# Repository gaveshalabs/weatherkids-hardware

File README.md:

# WeatherKids Weather Computer

WeatherKids is an engaging climate education program where children learn about climate change hands-on using a small, open-source weather station called the **Weather Computer**. This repository contains source code for both versions, **v1.0** and **v2.0**, of the Weather Computer. It is licensed under the **CERN Open Hardware License - W**, making it free to use, modify, and share in compliance with the license terms.

## Overview

The WeatherKids Weather Computer is designed to help young learners understand key aspects of weather and climate. Through real-time data collection and analysis, children learn about:

- Temperature
- Humidity
- Atmospheric Pressure
- And optional TVOC sensor

These metrics contribute to building awareness around climate science and inspire further exploration in STEM.

## Versions

### Version 1.0
- **Released**: 2022 December
- **Features**: 
    - Basic weather measurements (temperature, humidity,  pressure and optional TVOC sensor)
 
KNOWN issues - Charging mechanism doesn't work properly in fog conditions

### Version 2.0
- **Released**: 2023 December
- **Features**: 
    - Compact design with Li-Polimer battery
    - Sperate Action card to mearsure solar power and provide power to main board.

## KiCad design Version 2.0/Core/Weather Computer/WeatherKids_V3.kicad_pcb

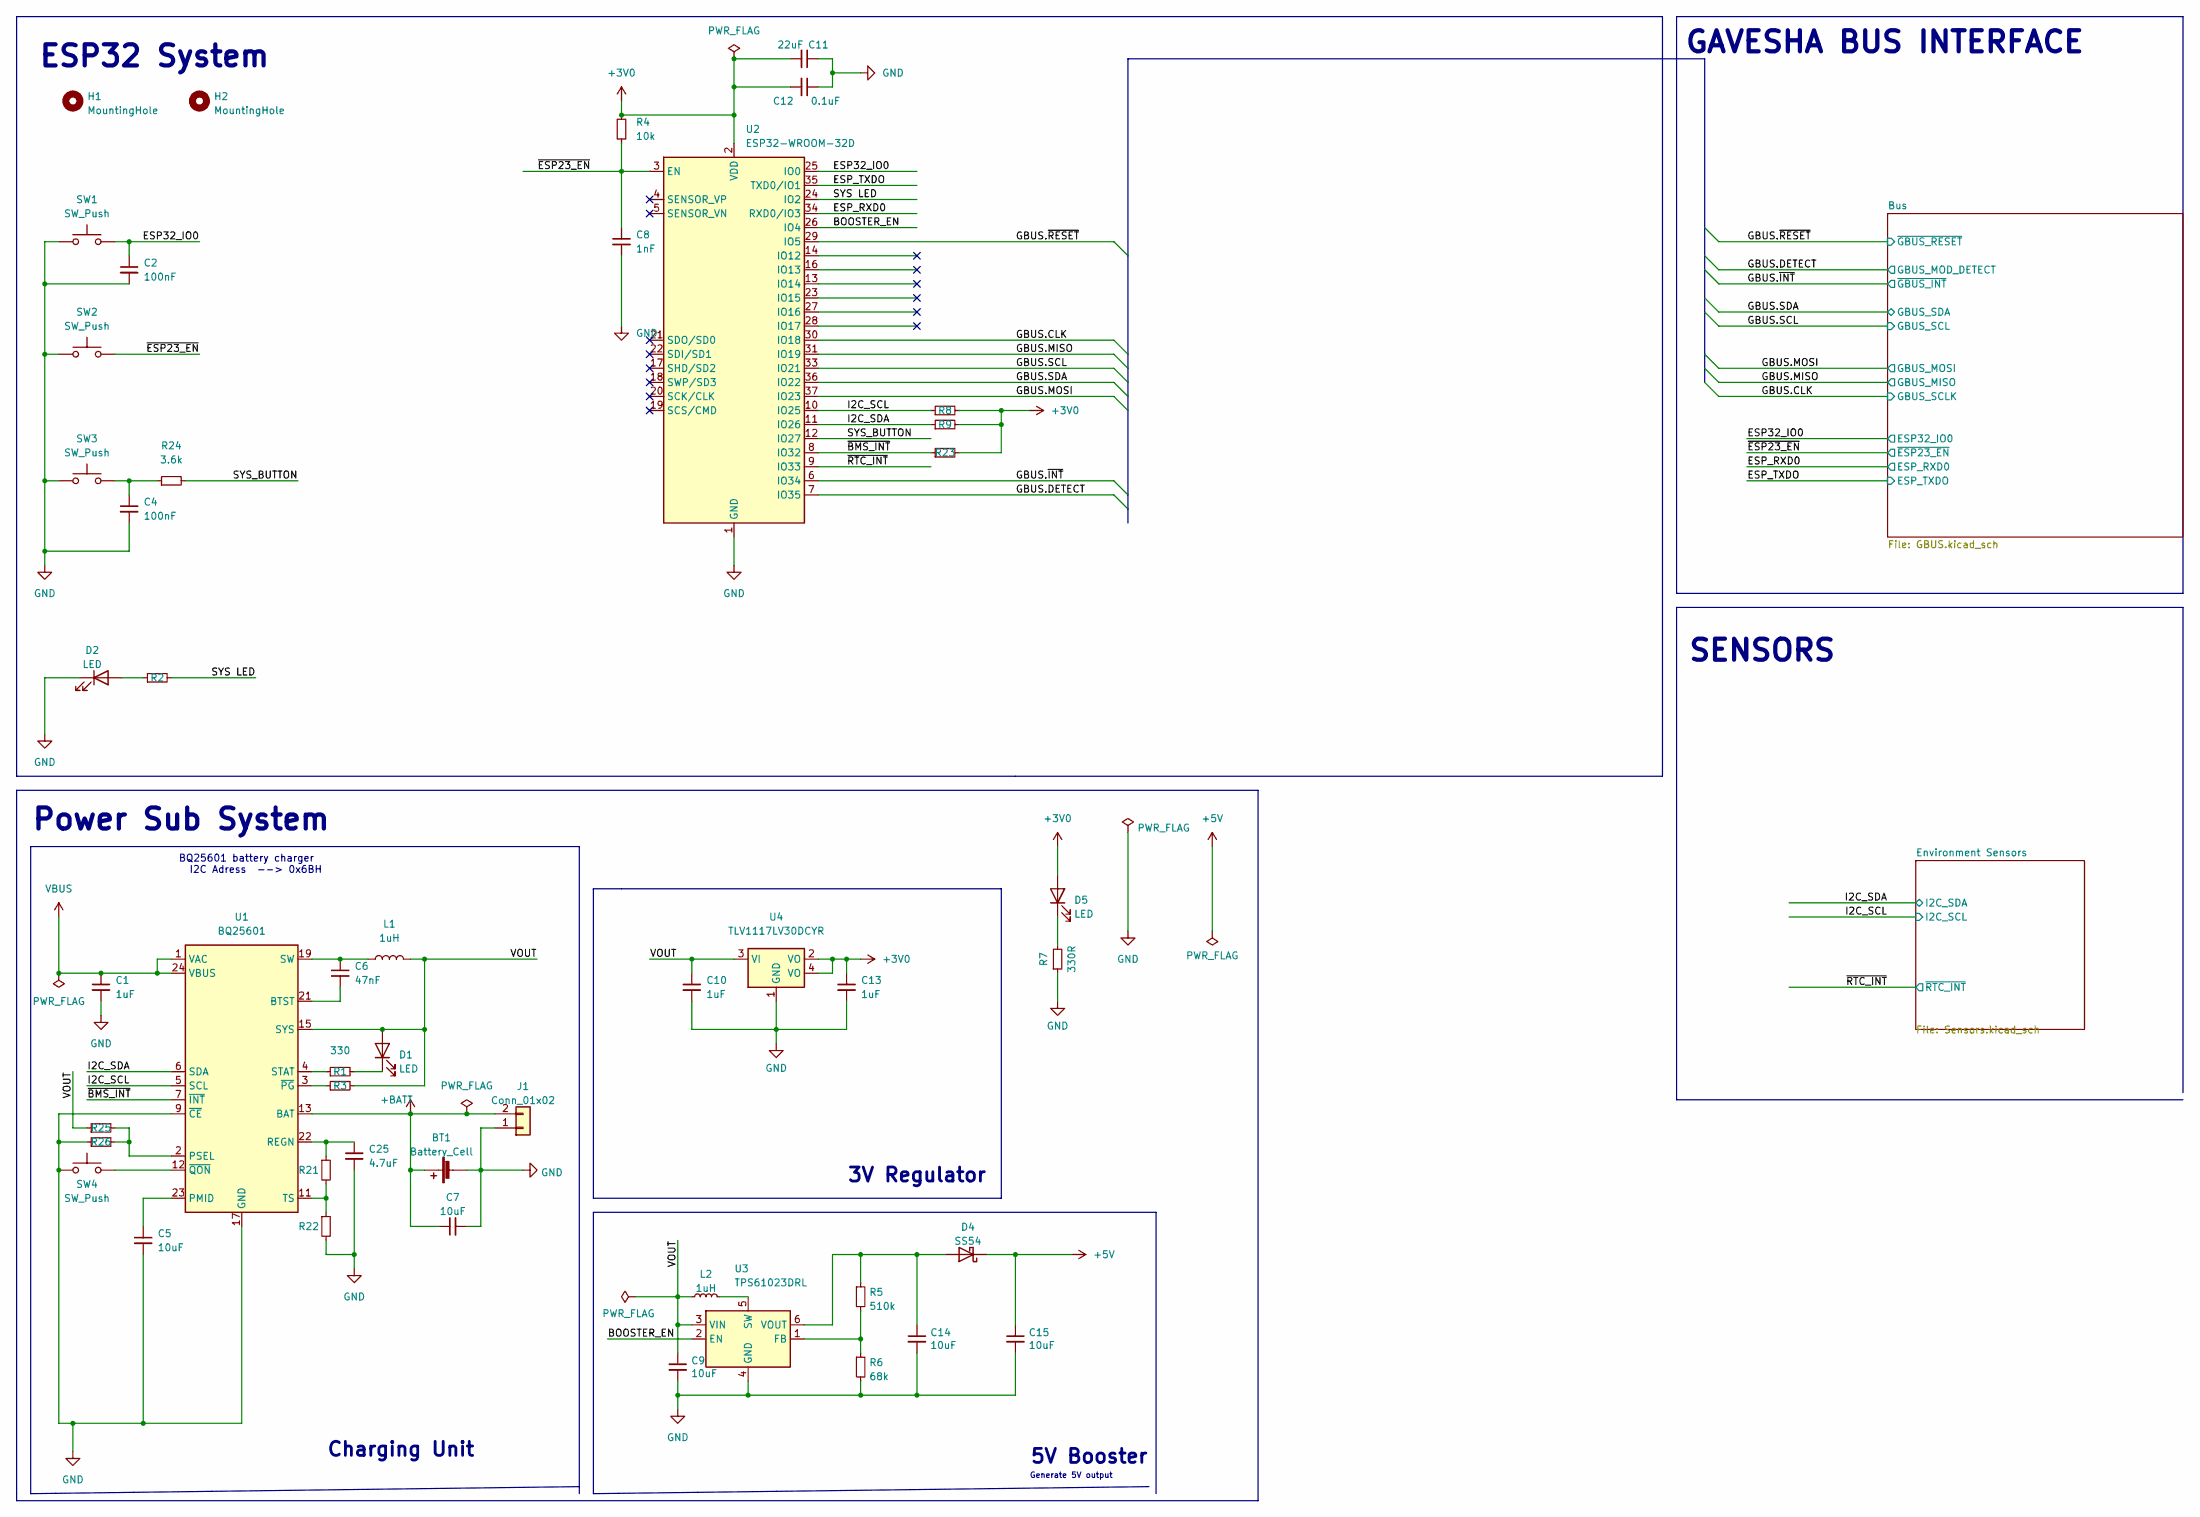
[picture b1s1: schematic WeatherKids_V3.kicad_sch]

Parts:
BT1: Battery_Cell; BatteryHolder_Keystone_1042_1x18650
C1, C10, C13: 1uF; C_0402_1005Metric
C2, C4: 100nF; C_0402_1005Metric
C5: 10uF; C_0402_1005Metric
C6: 47nF; C_0603_1608Metric
C7, C9, C14, C15: 10uF; C_0805_2012Metric
C8: 1nF; C_0402_1005Metric
C11: 22uF; C_0603_1608Metric
C12: 0.1uF; C_0402_1005Metric
C25: 4.7uF; C_0402_1005Metric
D1, D2, D5: LED; LED_0805_2012Metric
D4: SS54; D_SMA
H1, H2: MountingHole; MountingHole_2.2mm_M2
J1: Conn_01x02; JST_PH_S2B-PH-SM4-TB_1x02-1MP_P2.00mm_Horizontal
L1, L2: 1uH; WPN252010U
R1: 330; R_0402_1005Metric
R2, R7: 330R; R_0402_1005Metric
R3, R4, R8, R9, R21, R22, R23, R25, R26: 10k; R_0402_1005Metric
R5: 510k; R_0402_1005Metric
R6: 68k; R_0402_1005Metric
R24: 3.6k; R_0402_1005Metric
SW1, SW2, SW3, SW4: SW_Push; SKRTLB
U1: BQ25601; Texas_S-PWQFN-N24_EP2.7x2.7mm_ThermalVias
U2: ESP32-WROOM-32D; ESP32-WROOM-32
U3: TPS61023DRL; DRL0006A
U4: TLV1117LV30DCYR; SOT-223

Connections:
+3V0: C11.2, C12.2, C13.1, D5.2 (A), R4.1, R8.2, R9.2, R23.2, U2.2 (VDD), U4.2 (VO), U4.4 (VO); also elsewhere on the board
+5V: C15.1, D4.1 (K); also elsewhere on the board
+BATT: BT1.1 (+), C7.1, J1.2, U1.13 (BAT), U1.14 (BAT); also elsewhere on the board
/BOOSTER_EN: U2.26 (IO4), U3.2 (EN)
/ESP32_IO0: C2.1, SW1.2, U2.25 (IO0); also elsewhere on the board
/ESP_RXD0: U2.34 (RXD0/IO3); also elsewhere on the board
/ESP_TXDO: U2.35 (TXD0/IO1); also elsewhere on the board
/GBUS.CLK: U2.30 (IO18); also elsewhere on the board
/GBUS.DETECT: U2.7 (IO35); also elsewhere on the board
/GBUS.MISO: U2.31 (IO19); also elsewhere on the board
/GBUS.MOSI: U2.37 (IO23); also elsewhere on the board
/GBUS.SCL: U2.33 (IO21); also elsewhere on the board
/GBUS.SDA: U2.36 (IO22); also elsewhere on the board
/GBUS.~INT: U2.6 (IO34); also elsewhere on the board
/GBUS.~RESET: U2.29 (IO5); also elsewhere on the board
/I2C_SCL: R8.1, U1.5 (SCL), U2.10 (IO25); also elsewhere on the board
/I2C_SDA: R9.1, U1.6 (SDA), U2.11 (IO26); also elsewhere on the board
/SYS LED: R2.2, U2.24 (IO2)
/SYS_BUTTON: R24.2, U2.12 (IO27)
/VOUT: C9.1, C10.1, D1.2 (A), L1.2, L2.1, R3.2, R25.1, U1.15 (SYS), U1.16 (SYS), U3.3 (VIN), U4.3 (VI)
/~BMS_INT: R23.1, U1.7 (~INT), U2.8 (IO32)
/~ESP23_EN: C8.1, R4.2, SW2.2, U2.3 (EN); also elsewhere on the board
/~RTC_INT: U2.9 (IO33); also elsewhere on the board
GND: BT1.2 (-), C1.2, C2.2, C4.2, C5.2, C7.2, C8.2, C9.2, C10.2, C11.1, C12.1, C13.2, C14.2, C15.2, C25.2, D2.1 (K), J1.1, R6.2, R7.1, R22.2, R26.1, SW1.1, SW2.1, SW3.1, SW4.1, U1.9 (~CE), U1.17 (GND), U1.18 (GND), U1.25 (GND), U2.1 (GND), U2.15 (GND), U2.38 (GND), U2.39 (GND), U3.4 (GND), U4.1 (GND); also elsewhere on the board
unnamed: C4.1, R24.1, SW3.2
unnamed: C5.1, U1.23 (PMID)
unnamed: C6.1, L1.1, U1.19 (SW), U1.20 (SW)
unnamed: C6.2, U1.21 (BTST)
unnamed: C14.1, D4.2 (A), R5.1, U3.6 (VOUT)
unnamed: C25.1, R21.1, U1.22 (REGN)
unnamed: D1.1 (K), R1.2
unnamed: D2.2 (A), R2.1
unnamed: D5.1 (K), R7.2
unnamed: L2.2, U3.5 (SW)
unnamed: R1.1, U1.4 (STAT)
unnamed: R3.1, U1.3 (~PG)
unnamed: R5.2, R6.1, U3.1 (FB)
unnamed: R21.2, R22.1, U1.11 (TS)
unnamed: R25.2, R26.2, U1.2 (PSEL)
unnamed: SW4.2, U1.12 (~QON)
VBUS: C1.1, U1.1 (VAC), U1.24 (VBUS); also elsewhere on the board

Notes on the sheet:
5V Booster
SENSORS
Power Sub System
ESP32 System
3V Regulator
BQ25601 battery charger I2C Adress --> 0x6BH
Charging Unit
Generate 5V output
GAVESHA BUS INTERFACE

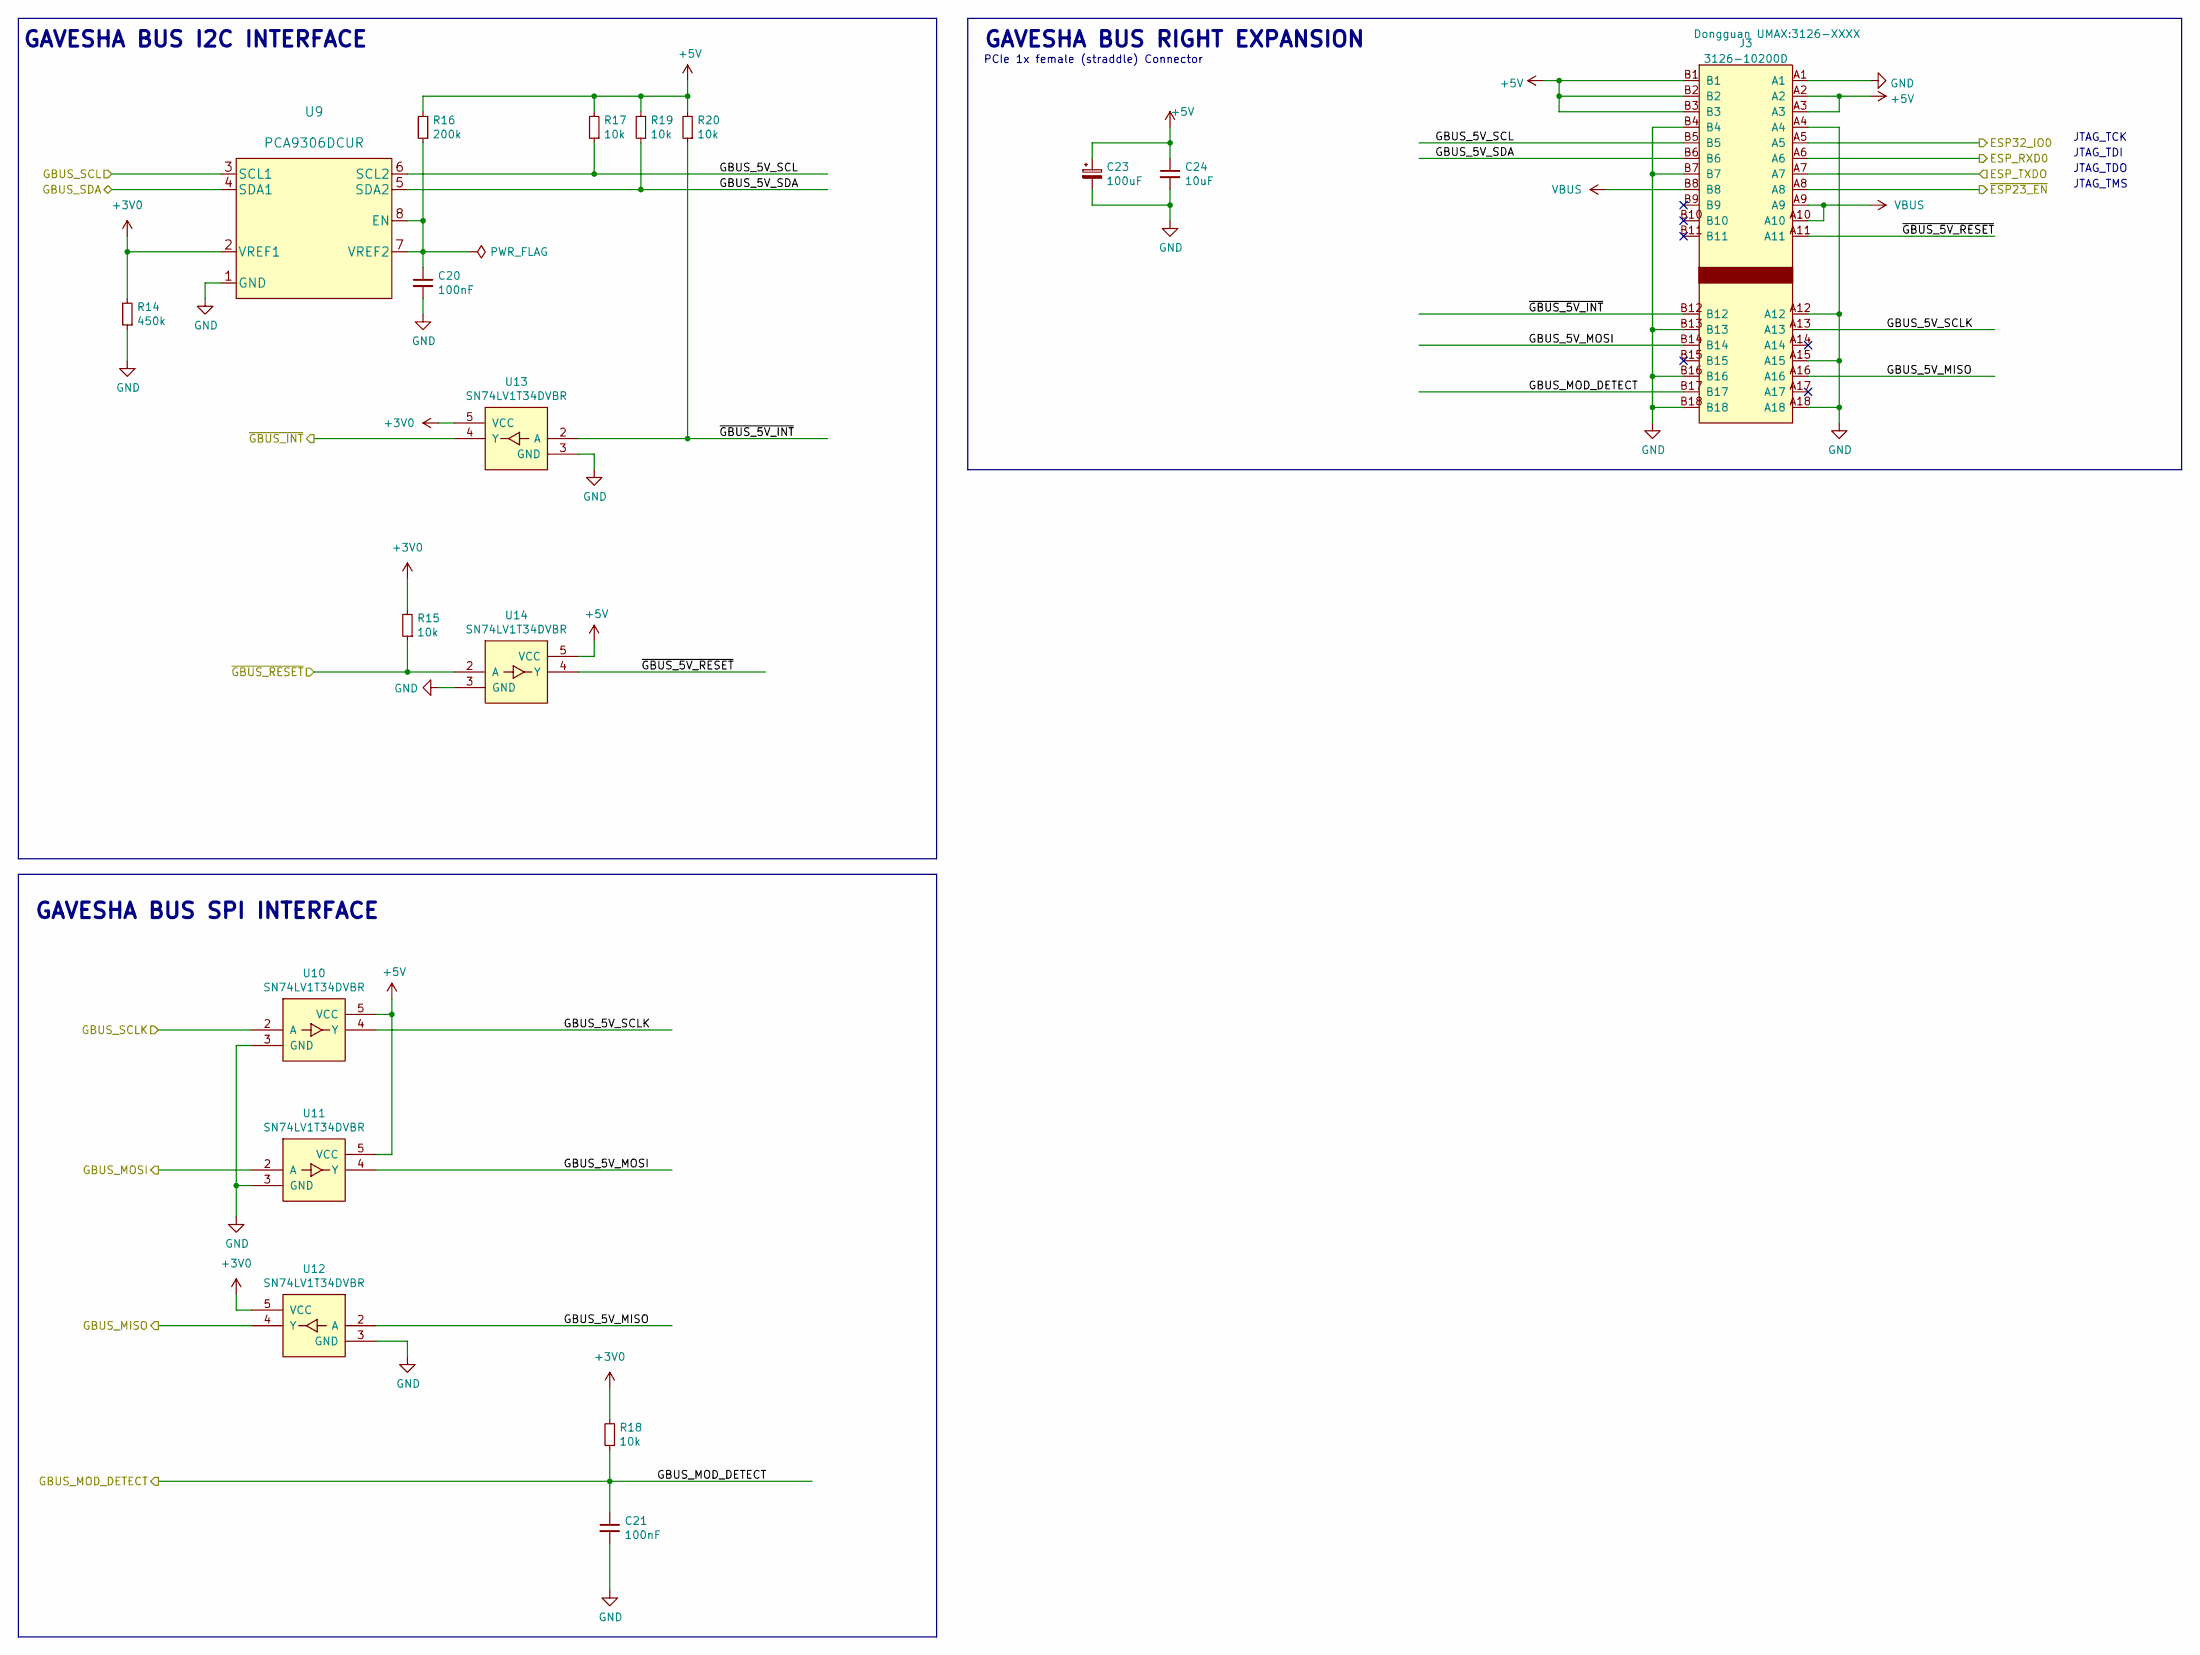
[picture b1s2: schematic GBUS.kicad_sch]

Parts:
C20, C21: 100nF; C_0402_1005Metric
C23: 100uF; CP_EIA-3528-12_Kemet-T
C24: 10uF; C_0805_2012Metric
J3: 3126-10200D; 3126-XXXX
R14: 450k; R_0402_1005Metric
R15, R17, R18, R19, R20: 10k; R_0402_1005Metric
R16: 200k; R_0402_1005Metric
U9: PCA9306DCUR
U10, U11, U12, U13, U14: SN74LV1T34DVBR; SOT-23-5

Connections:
+3V0: R14.2, R15.2, R18.2, U9.2 (VREF1), U12.5 (VCC), U13.5 (VCC); also elsewhere on the board
+5V: C23.1, C24.1, J3.A2, J3.A3, J3.B1, J3.B2, J3.B3, R16.2, R17.2, R19.2, R20.2, U10.5 (VCC), U11.5 (VCC), U14.5 (VCC); also elsewhere on the board
/Bus/GBUS_5V_MISO: J3.A16, U12.2 (A)
/Bus/GBUS_5V_MOSI: J3.B14, U11.4 (Y)
/Bus/GBUS_5V_SCL: J3.B5, R17.1, U9.6 (SCL2)
/Bus/GBUS_5V_SCLK: J3.A13, U10.4 (Y)
/Bus/GBUS_5V_SDA: J3.B6, R19.1, U9.5 (SDA2)
/Bus/~GBUS_5V_INT: J3.B12, R20.1, U13.2 (A)
/Bus/~GBUS_5V_RESET: J3.A11, U14.4 (Y)
/ESP32_IO0: J3.A5; also elsewhere on the board
/ESP_RXD0: J3.A6; also elsewhere on the board
/ESP_TXDO: J3.A7; also elsewhere on the board
/GBUS.CLK: U10.2 (A); also elsewhere on the board
/GBUS.DETECT: C21.1, J3.B17, R18.1; also elsewhere on the board
/GBUS.MISO: U12.4 (Y); also elsewhere on the board
/GBUS.MOSI: U11.2 (A); also elsewhere on the board
/GBUS.SCL: U9.3 (SCL1); also elsewhere on the board
/GBUS.SDA: U9.4 (SDA1); also elsewhere on the board
/GBUS.~INT: U13.4 (Y); also elsewhere on the board
/GBUS.~RESET: R15.1, U14.2 (A); also elsewhere on the board
/~ESP23_EN: J3.A8; also elsewhere on the board
GND: C20.2, C21.2, C23.2, C24.2, J3.A1, J3.A4, J3.A12, J3.A15, J3.A18, J3.B4, J3.B7, J3.B13, J3.B16, J3.B18, R14.1, U9.1 (GND), U10.3 (GND), U11.3 (GND), U12.3 (GND), U13.3 (GND), U14.3 (GND); also elsewhere on the board
unnamed: C20.1, R16.1, U9.7 (VREF2), U9.8 (EN)
VBUS: J3.A9, J3.A10, J3.B8; also elsewhere on the board

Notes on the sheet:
GAVESHA BUS I2C INTERFACE
JTAG_TDO
GAVESHA BUS SPI INTERFACE
JTAG_TDI
JTAG_TCK
PCIe 1x female (straddle) Connector
GAVESHA BUS RIGHT EXPANSION
JTAG_TMS

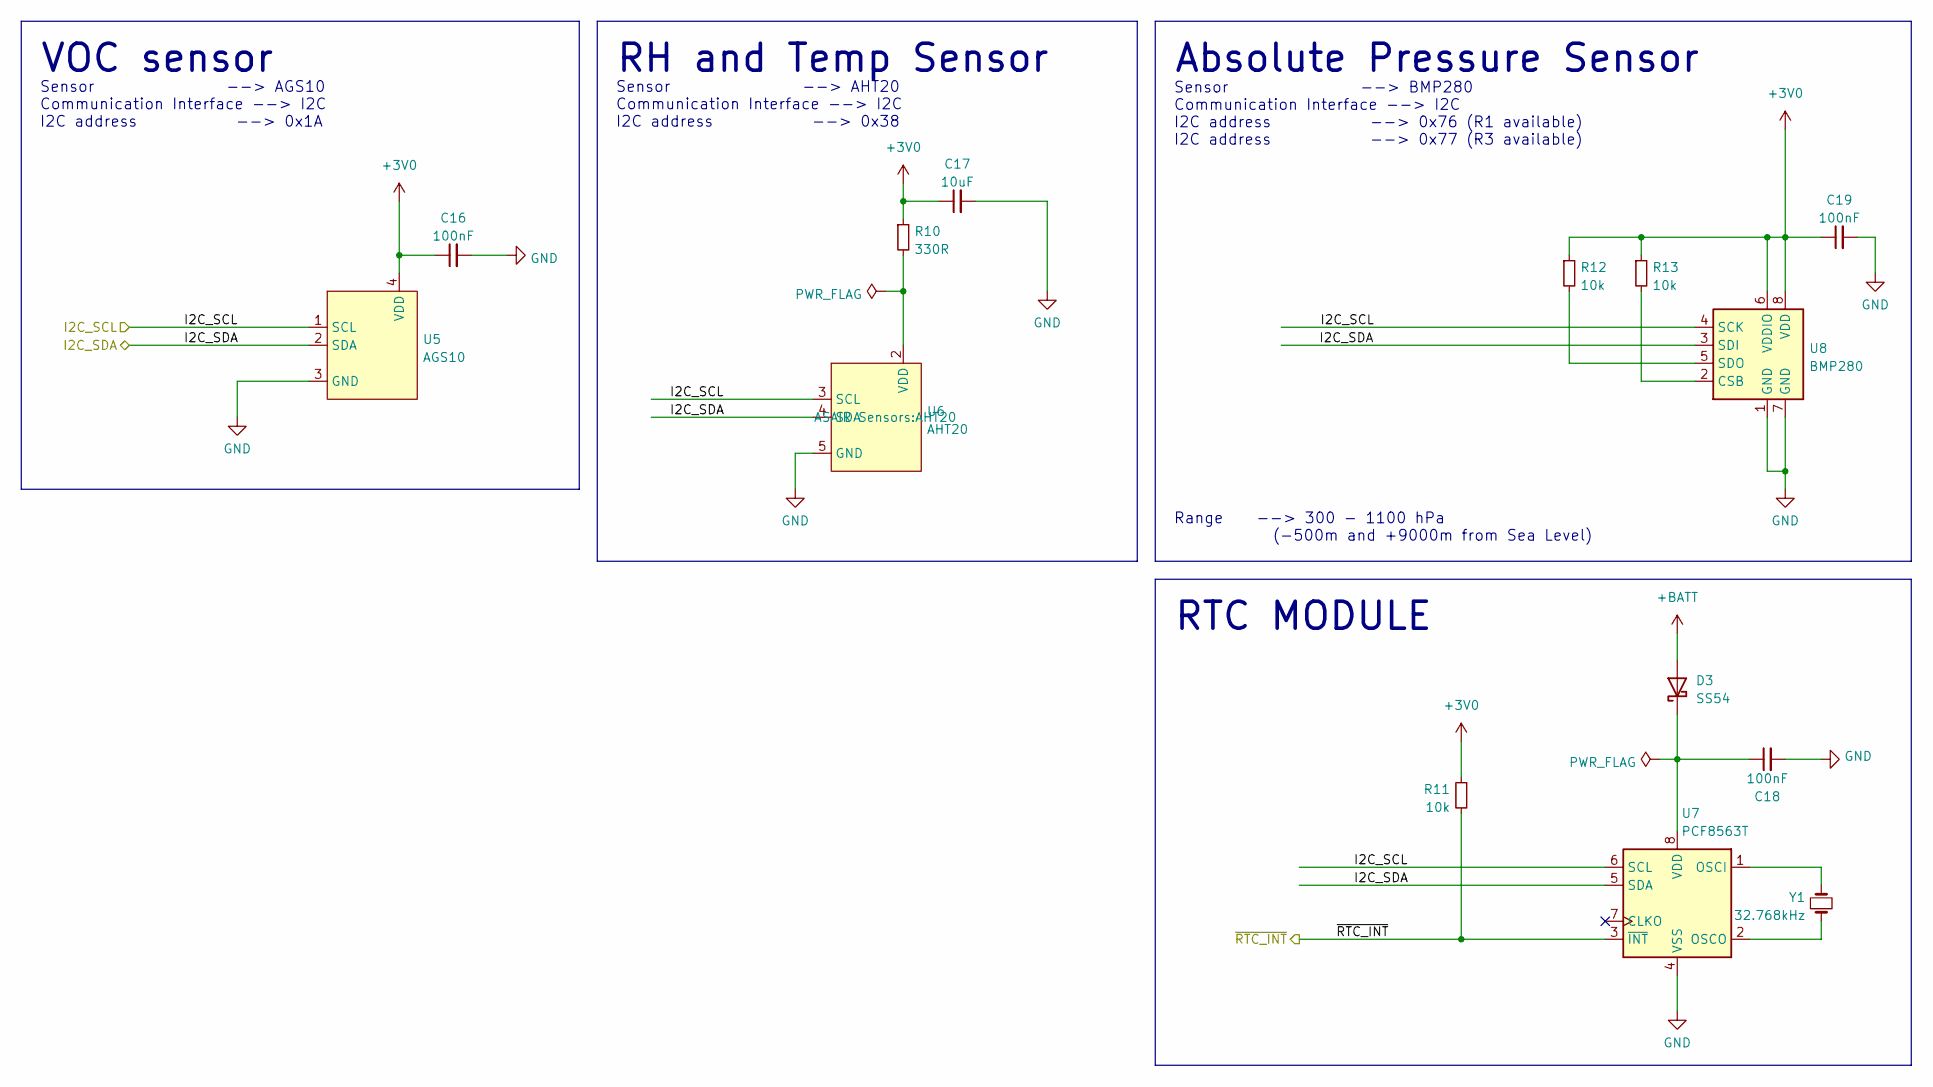
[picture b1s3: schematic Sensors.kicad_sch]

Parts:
C16, C18, C19: 100nF; C_0402_1005Metric
C17: 10uF; C_0805_2012Metric
D3: SS54; D_SOD-323; part no C2128
R10: 330R; R_0402_1005Metric
R11, R12, R13: 10k; R_0402_1005Metric
U5: AGS10
U6: AHT20
U7: PCF8563T; SOIC-8_3.9x4.9mm_P1.27mm
U8: BMP280; Bosch_LGA-8_2x2.5mm_P0.65mm_ClockwisePinNumbering
Y1: 32.768kHz; Crystal_SMD_3215-2Pin_3.2x1.5mm

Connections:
+3V0: C16.1, C17.1, C19.1, R10.1, R11.1, R12.1, R13.1, U5.4 (VDD), U8.6 (VDDIO), U8.8 (VDD); also elsewhere on the board
+BATT: D3.2 (A); also elsewhere on the board
/I2C_SCL: U5.1 (SCL), U6.3 (SCL), U7.6 (SCL), U8.4 (SCK); also elsewhere on the board
/I2C_SDA: U5.2 (SDA), U6.4 (SDA), U7.5 (SDA), U8.3 (SDI); also elsewhere on the board
/~RTC_INT: R11.2, U7.3 (~INT); also elsewhere on the board
GND: C16.2, C17.2, C18.2, C19.2, U5.3 (GND), U6.5 (GND), U7.4 (VSS), U8.1 (GND), U8.7 (GND); also elsewhere on the board
unnamed: C18.1, D3.1 (K), U7.8 (VDD)
unnamed: R10.2, U6.2 (VDD)
unnamed: R12.2, U8.5 (SDO)
unnamed: R13.2, U8.2 (CSB)
unnamed: U7.1 (OSCI), Y1.2
unnamed: U7.2 (OSCO), Y1.1

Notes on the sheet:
Sensor --> AGS10 Communication Interface --> I2C I2C address --> 0x1A
Sensor --> BMP280 Communication Interface --> I2C I2C address --> 0x76 (R1 available) I2C address --> 0x77 (R3 available)
Range --> 300 - 1100 hPa (-500m and +9000m from Sea Level)
RH and Temp Sensor
RTC MODULE
Sensor --> AHT20 Communication Interface --> I2C I2C address --> 0x38
VOC sensor
Absolute Pressure Sensor

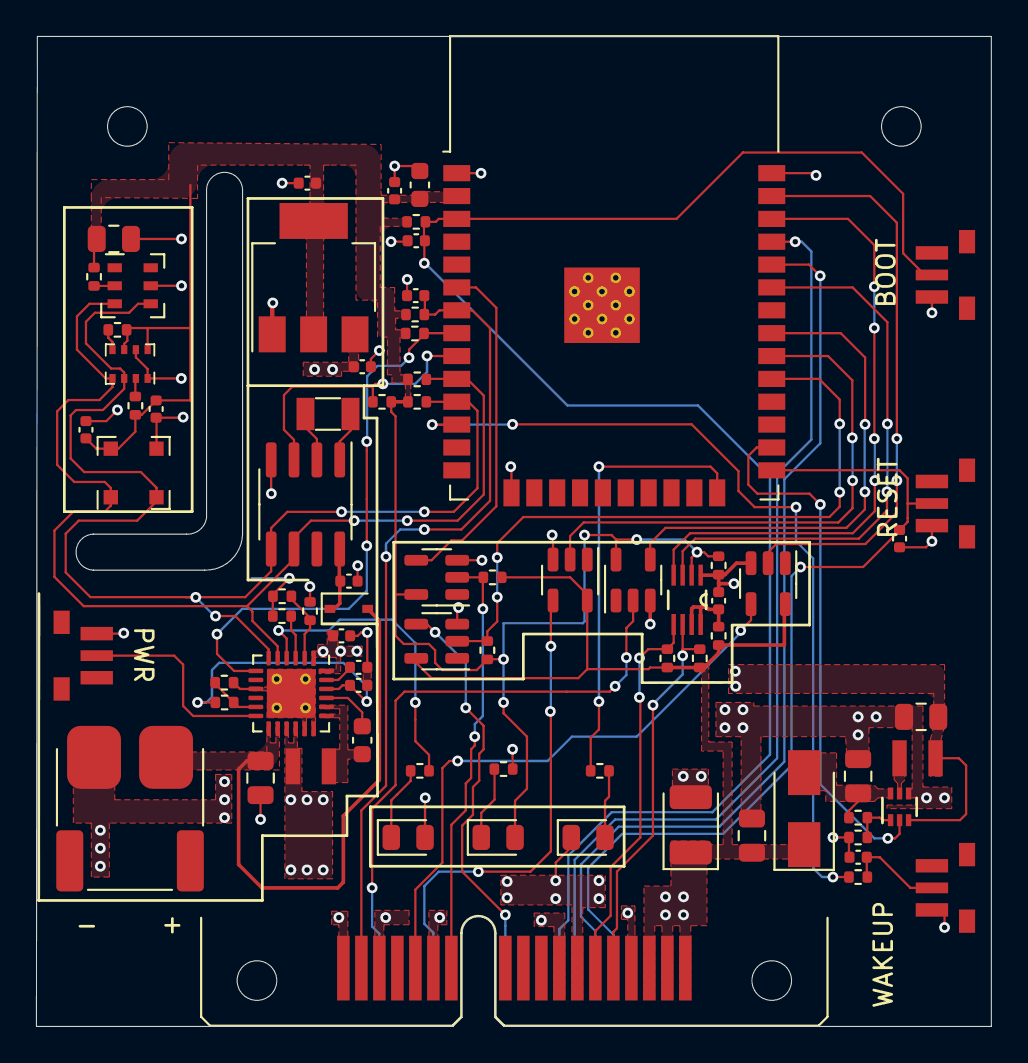
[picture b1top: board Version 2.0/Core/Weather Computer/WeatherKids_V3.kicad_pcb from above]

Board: 2 copper layers, 53.0 x 55.0 mm, 78 parts (0 on the bottom side), 55 nets.

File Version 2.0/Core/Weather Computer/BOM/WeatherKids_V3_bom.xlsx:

Designator | Footprint | Value | JLCPCB Part #
C1, C10, C13 | 402 | 1uF | C52923
C11 | 603 | 22uF | C59461
C14, C15, C17, C24, C7, C9 | 805 | 10uF | C15850
C16, C18, C19, C2, C20, C21, C4 | 402 | 100nF | C1525
C23 | CP_EIA-3528-12_Kemet-T | 100uF | C16133
C25 | 402 | 4.7uF | C23733
C5 | 402 | 10uF | C15525
C6 | 603 | 47nF | C1622
C8 | 402 | 1nF | C1523
D1, D2, D5 | 805 | LED | C34499
D3 | D_SOD-323 | 1N4148WS | C2128
D4 | D_SMA | SS54 | C22452
J1 | JST_PH_S2B-PH-SM4-TB_1x02-1MP_P2.00mm_Horizontal | Conn_01x02 | C295747
L1, L2 | WPN252010U | 1uH | C279952
R10, R2, R7 | 402 | 330R | C25104
R3,R11, R12, R13, R15, R17, R18, R19, R20, R21, R22, R23, R4, R8, R9 | 402 | 10k | C25744
R16 | 402 | 200k | C25764
R24 | 402 | 3.6k | C310258
R5 | 402 | 510k | C11616
R6 | 402 | 68k | C36871
SW1, SW2, SW3, SW4 | SKRTLB | SW_Push | C127481
U1 | Texas_S-PWQFN-N24_EP2.7x2.7mm_ThermalVias | BQ25601 | C468236
U10, U11, U12, U13, U14 | SOT-23-5 | SN74LV1T34DVBR | C100024
U3 | DRL0006A | TPS61023DRL | C919459
U4 | SOT-223 | TLV1117LV30DCYR | C507264
U5 | AGS10 | AGS10 | C3012632
U6 | AHT20 | AHT20 | C3012622 | C2757850
U7 | SOIC-8_3.9x4.9mm_P1.27mm | PCF8563T | C7440
U8 | Bosch_LGA-8_2x2.5mm_P0.65mm_ClockwisePinNumbering | BMP280 | C83291
U9 | PCA9306DCUR | PCA9306DCUR | C33196
Y1 | Crystal_SMD_3215-2Pin_3.2x1.5mm | 32.768kHz | C32346
U2 | ESP32-WROOM-32 | ESP32-WROOM-32D | C701342

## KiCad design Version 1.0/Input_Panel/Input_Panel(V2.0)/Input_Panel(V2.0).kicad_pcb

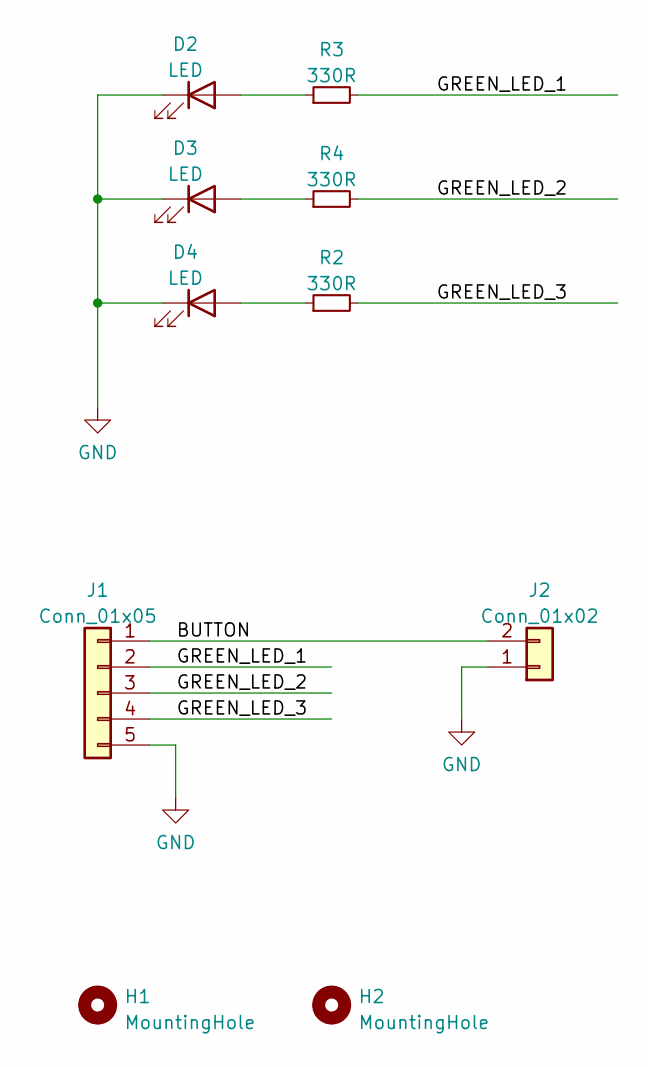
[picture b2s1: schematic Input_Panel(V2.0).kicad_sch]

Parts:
D2, D3, D4: LED; LED_D5.0mm
H1, H2: MountingHole; MountingHole_3.2mm_M3
J1: Conn_01x05; JST_PH_B5B-PH-K_1x05_P2.00mm_Vertical
J2: Conn_01x02; JST_PH_B2B-PH-K_1x02_P2.00mm_Vertical
R2, R3, R4: 330R; R_Axial_DIN0207_L6.3mm_D2.5mm_P10.16mm_Horizontal

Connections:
/BUTTON: J1.1, J2.2
/GREEN_LED_1: J1.2, R3.2
/GREEN_LED_2: J1.3, R4.2
/GREEN_LED_3: J1.4, R2.2
GND: D2.1 (K), D3.1 (K), D4.1 (K), J1.5, J2.1
unnamed: D2.2 (A), R3.1
unnamed: D3.2 (A), R4.1
unnamed: D4.2 (A), R2.1

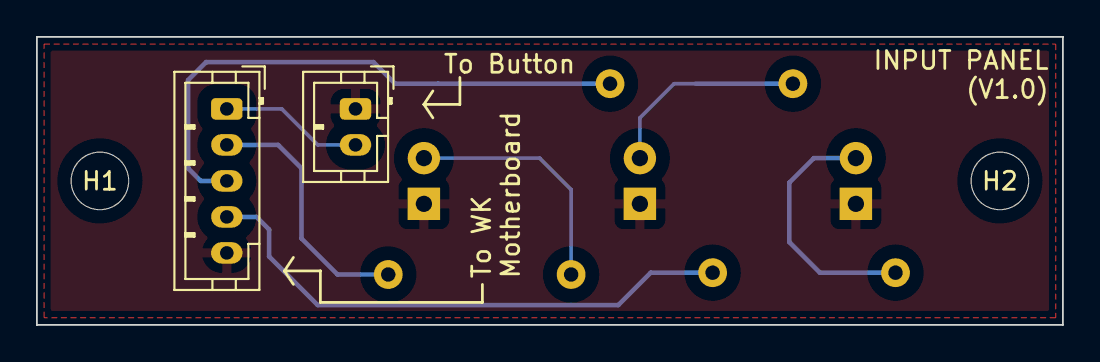
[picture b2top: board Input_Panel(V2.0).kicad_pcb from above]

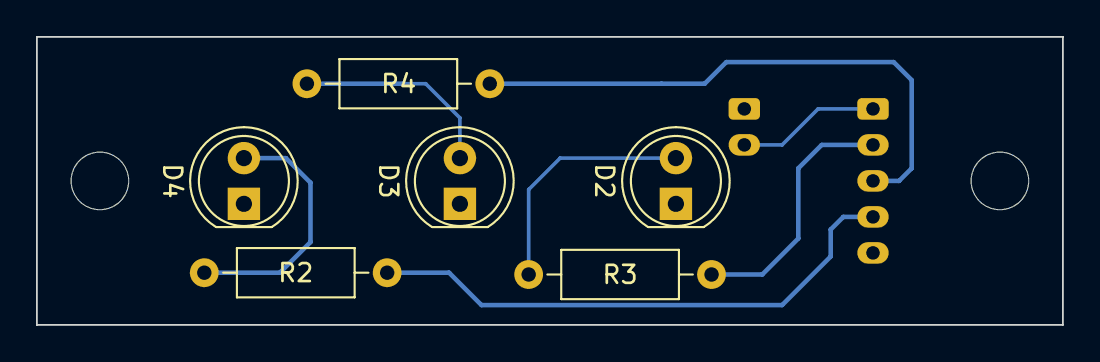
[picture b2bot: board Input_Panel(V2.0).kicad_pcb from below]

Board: 2 copper layers, 57.0 x 16.0 mm, 10 parts (6 on the bottom side), 8 nets.

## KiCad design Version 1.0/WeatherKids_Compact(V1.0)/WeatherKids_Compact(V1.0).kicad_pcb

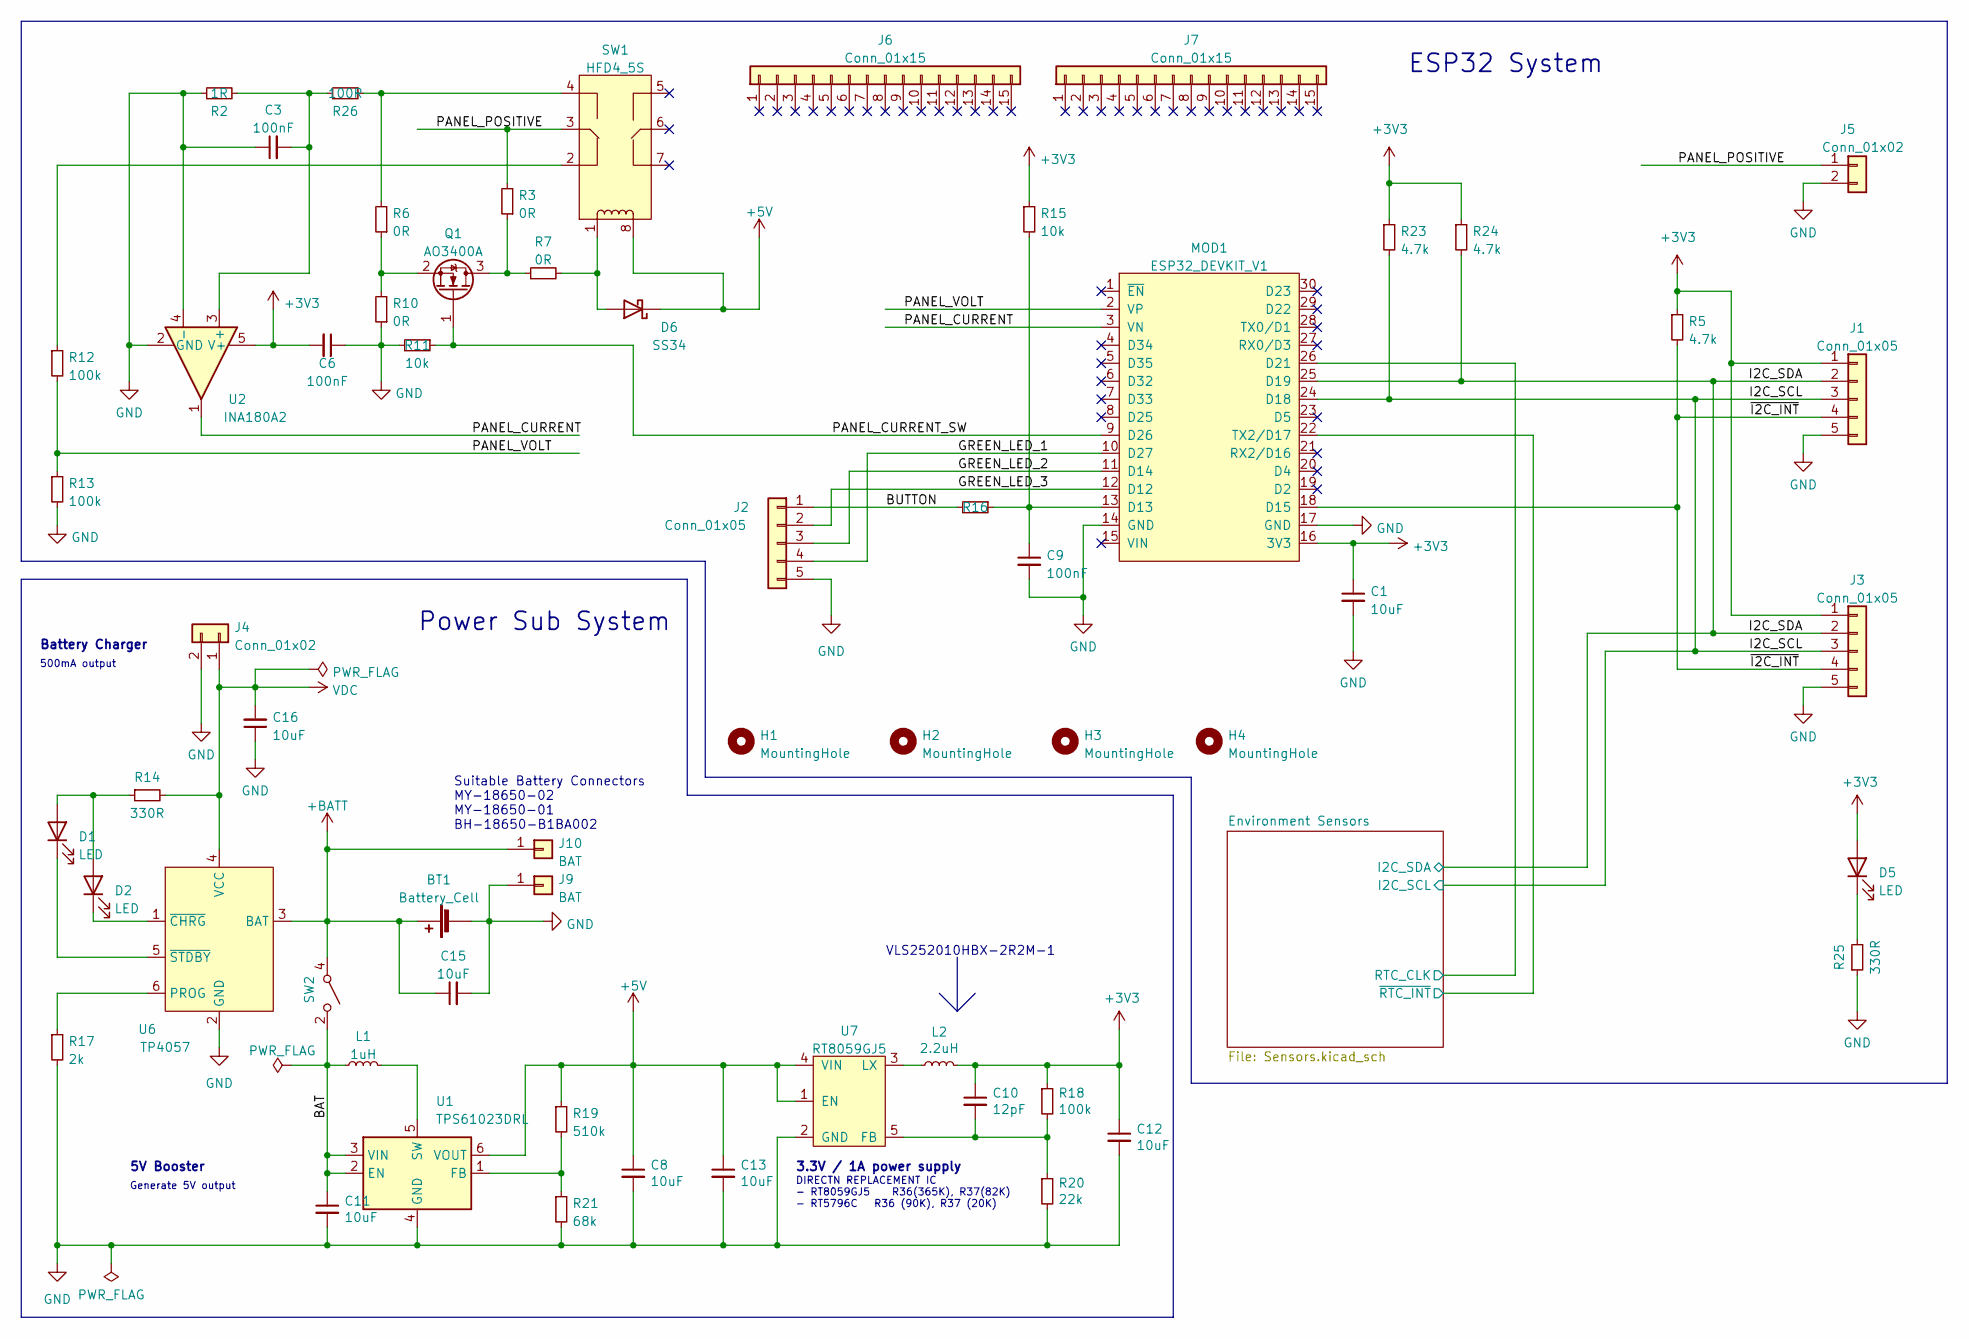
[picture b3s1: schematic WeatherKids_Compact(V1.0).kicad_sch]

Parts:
BT1: Battery_Cell; BatteryHolder_Keystone_1042_1x18650
C1: 10uF
C3, C6, C9: 100nF; C_0402_1005Metric
C8, C11, C12, C13, C15, C16: 10uF; C_0805_2012Metric
C10: 12pF; C_0402_1005Metric
D1, D2, D5: LED; LED_0805_2012Metric
D6: SS34; D_SMA
H1, H2, H3, H4: MountingHole; MountingHole_2.2mm_M2
J1, J2, J3: Conn_01x05; JST_PH_S5B-PH-K_1x05_P2.00mm_Horizontal
J4, J5: Conn_01x02; JST_PH_S2B-PH-K_1x02_P2.00mm_Horizontal
J6, J7: Conn_01x15; PinSocket_1x15_P2.54mm_Vertical
J9, J10: BAT; MY-18650-01
L1: 1uH; WPN252010U
L2: 2.2uH; WPN252010U
MOD1: ESP32_DEVKIT_V1; ESP32_DEVKIT_V1.0
Q1: AO3400A; SOT-23
R2: 1R; R_1206_3216Metric
R3, R6, R7, R10: 0R; R_0402_1005Metric
R5, R23, R24: 4.7k; R_0402_1005Metric
R11, R15: 10k; R_0402_1005Metric
R12, R13, R18: 100k; R_0402_1005Metric
R14, R25: 330R; R_0402_1005Metric
R16: 1k; R_0402_1005Metric
R17: 2k; R_0603_1608Metric
R19: 510k; R_0402_1005Metric
R20: 22k; R_0402_1005Metric
R21: 68k; R_0402_1005Metric
R26: 100R; R_1206_3216Metric
SW1: HFD4_5S; HDF4
SW2: SW_SPST; XKB5858-X-E
U1: TPS61023DRL; DRL0006A
U2: INA180A2; SOT-23-5
U6: TP4057; SOT-23-6
U7: RT8059GJ5; TSOT-23-5

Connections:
+3V3: C1.1, C6.2, C10.1, C12.1, D5.2 (A), J1.1, J3.1, L2.2, MOD1.16 (3V3), R5.1, R15.1, R18.1, R23.1, R24.1, U2.5 (V+); also elsewhere on the board
+5V: C8.1, C13.1, D6.1 (K), R19.1, SW1.8, U1.6 (VOUT), U7.1 (EN), U7.4 (VIN)
+BATT: BT1.1 (+), C15.1, J10.1, SW2.4 (A), U6.3 (BAT); also elsewhere on the board
/BAT: C11.1, L1.1, SW2.2 (B), U1.2 (EN), U1.3 (VIN)
/BUTTON: J2.1, R16.2
/Environment Sensors/RTC_CLK: MOD1.26 (D21); also elsewhere on the board
/Environment Sensors/~RTC_INT: MOD1.22 (TX2/D17); also elsewhere on the board
/GREEN_LED_1: J2.4, MOD1.10 (D27)
/GREEN_LED_2: J2.3, MOD1.11 (D14)
/GREEN_LED_3: J2.2, MOD1.12 (D12)
/I2C_SCL: J1.3, J3.3, MOD1.24 (D18), R23.2; also elsewhere on the board
/I2C_SDA: J1.2, J3.2, MOD1.25 (D19), R24.2; also elsewhere on the board
/PANEL_CURRENT: MOD1.3 (VN), U2.1
/PANEL_CURRENT_SW: MOD1.9 (D26), Q1.1 (G), R11.1
/PANEL_POSITIVE: J5.1, R3.2, SW1.3
/PANEL_VOLT: MOD1.2 (VP), R12.2, R13.1
/~I2C_INT: J1.4, J3.4, MOD1.18 (D15), R5.2
GND: BT1.2 (-), C1.2, C3.1, C6.1, C8.2, C9.2, C11.2, C12.2, C13.2, C15.2, C16.1, J1.5, J2.5, J3.5, J4.2, J5.2, J9.1, MOD1.14 (GND), MOD1.17 (GND), R2.1, R10.1, R11.2, R13.2, R17.2, R20.2, R21.2, R25.1, U1.4 (GND), U2.2 (GND), U2.4 (-), U6.2 (GND), U7.2 (GND); also elsewhere on the board
unnamed: C3.2, R2.2, R26.2, U2.3 (+)
unnamed: C9.1, MOD1.13 (D13), R15.2, R16.1
unnamed: C10.2, R18.2, R20.1, U7.5 (FB)
unnamed: D1.1 (K), U6.5 (~STDBY)
unnamed: D1.2 (A), D2.2 (A), R14.1
unnamed: D2.1 (K), U6.1 (~CHRG)
unnamed: D5.1 (K), R25.2
unnamed: D6.2 (A), R7.2, SW1.1
unnamed: L1.2, U1.5 (SW)
unnamed: L2.1, U7.3 (LX)
unnamed: Q1.2 (S), R6.1, R10.2
unnamed: Q1.3 (D), R3.1, R7.1
unnamed: R12.1, SW1.2
unnamed: R17.1, U6.6 (PROG)
unnamed: R19.2, R21.1, U1.1 (FB)
unnamed: R6.2, R26.1, SW1.4
VDC: C16.2, J4.1, R14.2, U6.4 (VCC)

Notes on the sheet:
Battery Charger
VLS252010HBX-2R2M-1
Power Sub System
Suitable Battery Connectors MY-18650-02 MY-18650-01 BH-18650-B1BA002
500mA output
DIRECTN REPLACEMENT IC - RT8059GJ5 R36(365K), R37(82K) - RT5796C R36 (90K), R37 (20K)
ESP32 System
5V Booster
Generate 5V output
3.3V / 1A power supply

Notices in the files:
parts and their libraries:
Copyright 2016 Accelerated Designs. All rights reserved.
